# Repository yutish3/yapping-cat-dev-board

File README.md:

this is a custom made esp 32 devboard with extra 128mbit memory so it can do a little more processing then normal
it also has intigrted sensors for temprature and gyromovement sd card slot andd headphone jack
this will fit my custom need of small yet powerful enough custom devboard

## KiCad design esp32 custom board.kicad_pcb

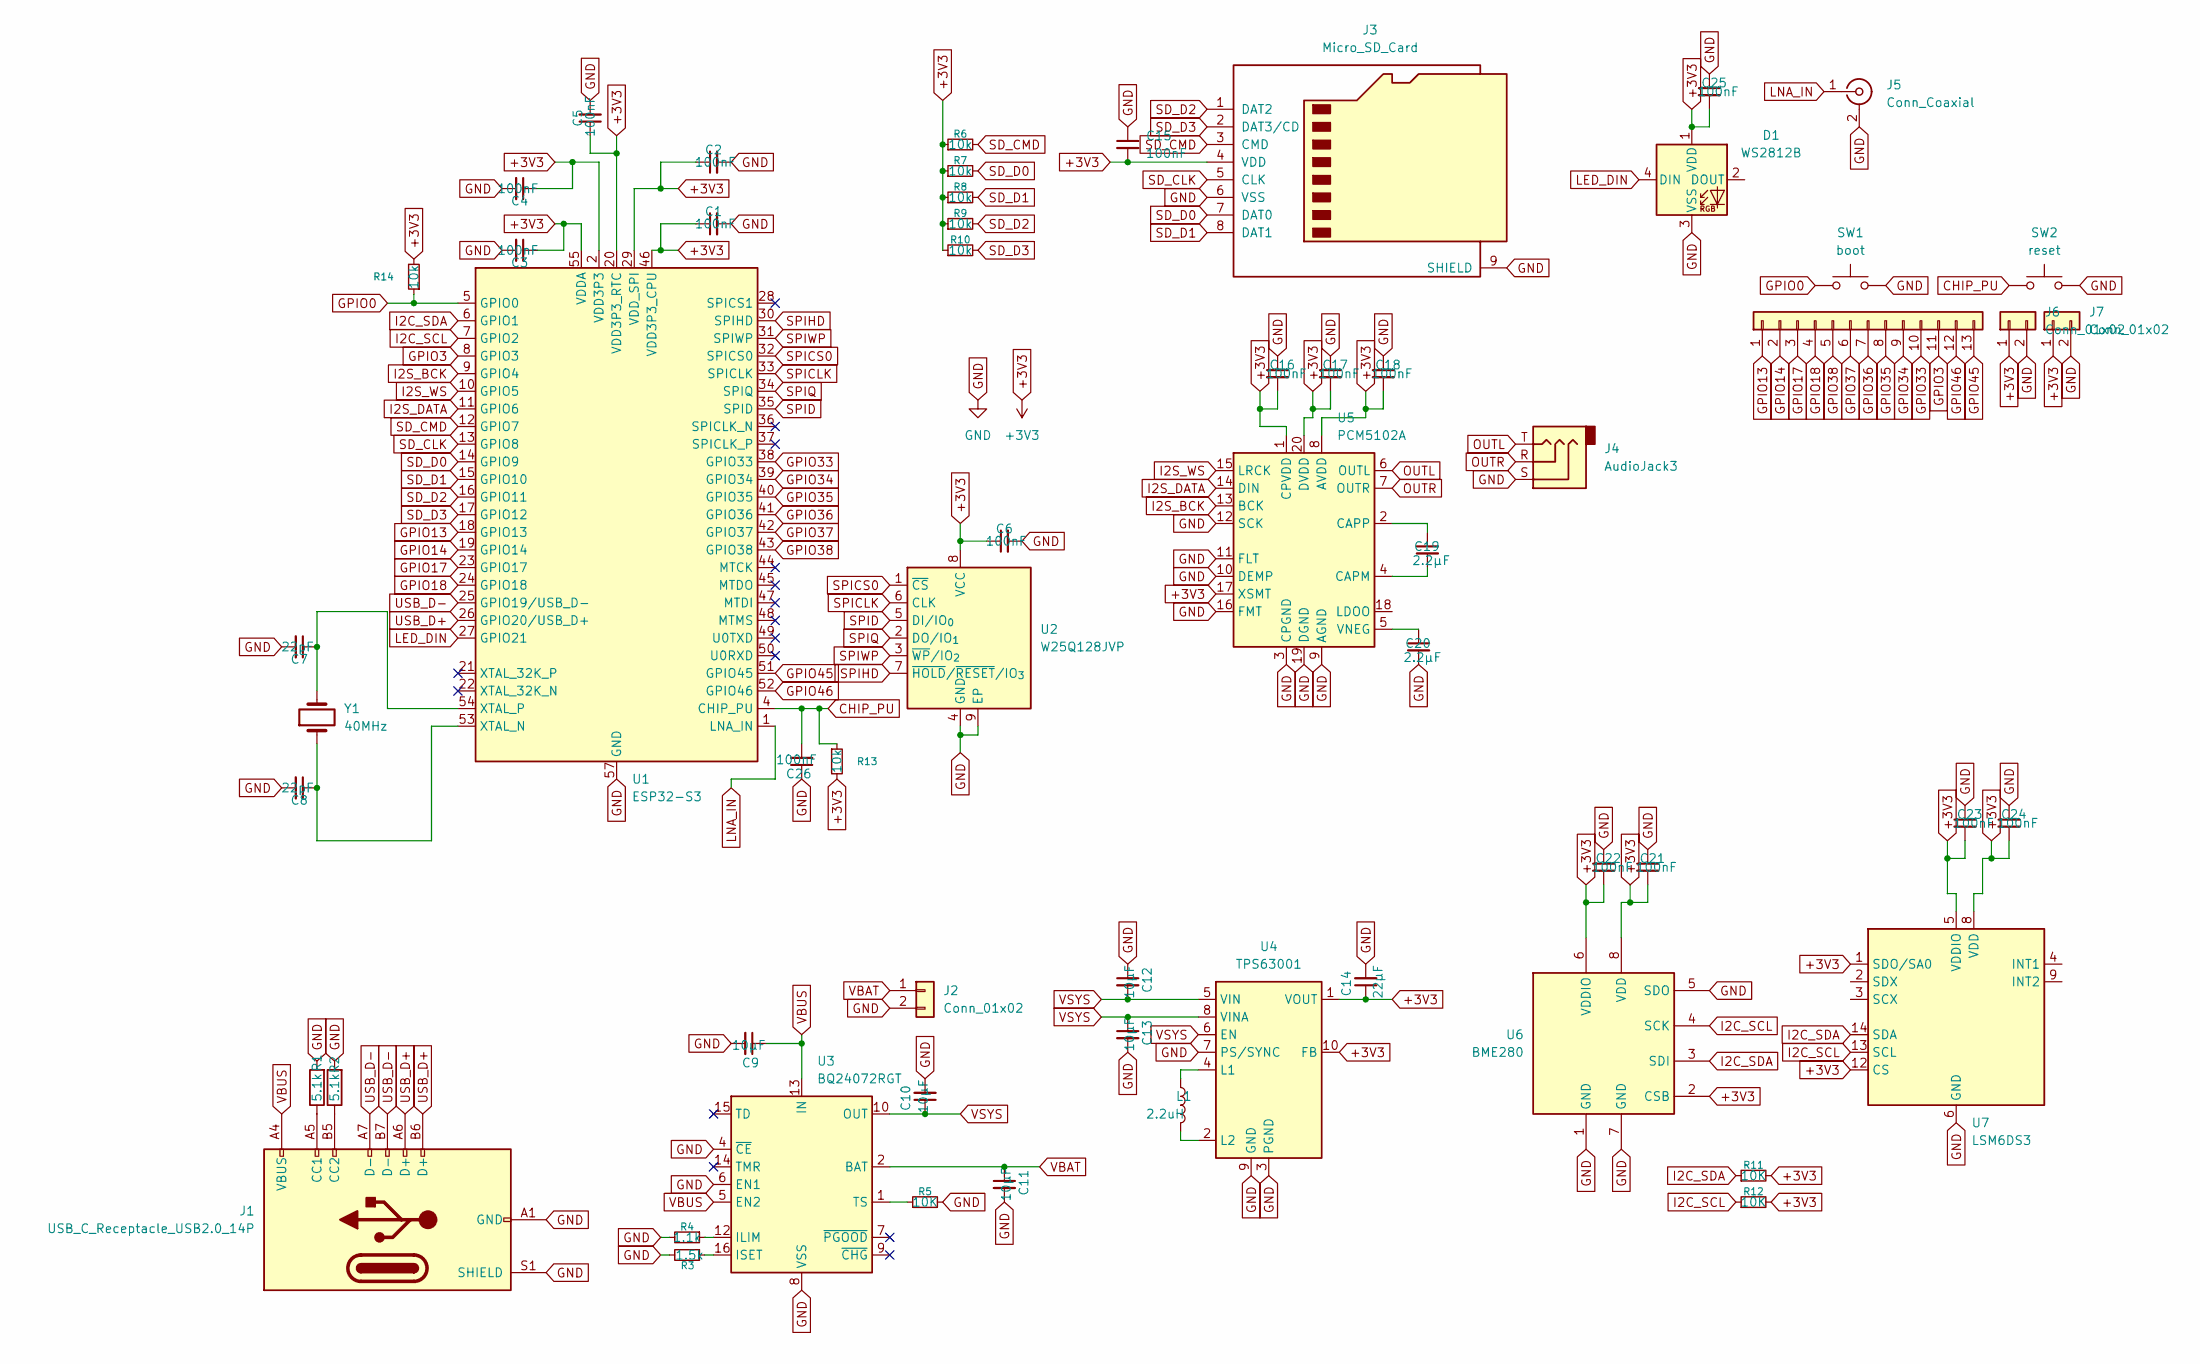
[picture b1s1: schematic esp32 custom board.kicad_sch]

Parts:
C1, C2, C3, C4, C5, C6, C15, C16, C17, C18, C21, C22, C23, C24, C25, C26: 100nF; C_0603_1608Metric
C7, C8: 22pF; C_0603_1608Metric
C9, C10, C11, C12, C13: 10µF; C_0603_1608Metric
C14: 22µF; C_0603_1608Metric
C19, C20: 2.2µF; C_0603_1608Metric
D1: WS2812B; LED_WS2812B_PLCC4_5.0x5.0mm_P3.2mm
J1: USB_C_Receptacle_USB2.0_14P; USB_C_Receptacle_Amphenol_124019772112A
J2: Conn_01x02; JST_PH_S2B-PH-SM4-TB_1x02-1MP_P2.00mm_Horizontal
J3: Micro_SD_Card; microSD_HC_Hirose_DM3AT-SF-PEJM5
J4: AudioJack3; Jack_3.5mm_CUI_SJ-3523-SMT_Horizontal
J5: Conn_Coaxial; U.FL_Hirose_U.FL-R-SMT-1_Vertical
J6, J7: Conn_01x02; PinHeader_1x02_P2.54mm_Vertical
J8: Conn_01x13; PinHeader_1x13_P2.54mm_Vertical
L1: 2.2uH; L_6.3x6.3_H3
R1, R2: 5.1k; R_0603_1608Metric
R3: 1.5k; R_0603_1608Metric
R4: 1.1k; R_0603_1608Metric
R5, R11, R12: 10K; R_0603_1608Metric
R6, R7, R8, R9, R10, R13, R14: 10k; R_0603_1608Metric
SW1: boot; SW_SPST_FSMSM
SW2: reset; SW_SPST_FSMSM
U1: ESP32-S3; QFN-56-1EP_7x7mm_P0.4mm_EP4x4mm
U2: W25Q128JVP; WSON-8-1EP_6x5mm_P1.27mm_EP3.4x4.3mm
U3: BQ24072RGT; VQFN-16-1EP_3x3mm_P0.5mm_EP1.6x1.6mm
U4: TPS63001; Texas_DRC0010J_ThermalVias
U5: PCM5102A; TSSOP-20_4.4x6.5mm_P0.65mm
U6: BME280; Bosch_LGA-8_2.5x2.5mm_P0.65mm_ClockwisePinNumbering
U7: LSM6DS3; LGA-14_3x2.5mm_P0.5mm_LayoutBorder3x4y
Y1: 40MHz; Crystal_SMD_3225-4Pin_3.2x2.5mm

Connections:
+3V3: C1.1, C2.1, C3.1, C4.1, C5.1, C6.1, C14.1, C15.2, C16.2, C17.2, C18.2, C21.2, C22.2, C23.2, C24.2, C25.2, D1.1 (VDD), J3.4 (VDD), J6.1, J7.1, R6.1, R7.1, R8.1, R9.1, R10.1, R11.2, R12.2, R13.2, R14.2, U1.2 (VDD3P3), U1.3 (VDD3P3), U1.20 (VDD3P3_RTC), U1.29 (VDD_SPI), U1.46 (VDD3P3_CPU), U1.55 (VDDA), U1.56 (VDDA), U2.8 (VCC), U4.1 (VOUT), U4.10 (FB), U5.1 (CPVDD), U5.8 (AVDD), U5.17 (XSMT), U5.20 (DVDD), U6.2 (CSB), U6.6 (VDDIO), U6.8 (VDD), U7.1 (SDO/SA0), U7.5 (VDDIO), U7.8 (VDD), U7.12 (CS)
CHIP_PU: C26.2, R13.1, SW2.1, U1.4 (CHIP_PU)
GND: C1.2, C2.2, C3.2, C4.2, C5.2, C6.2, C7.2, C8.2, C9.2, C10.2, C11.2, C12.1, C13.2, C14.2, C15.1, C16.1, C17.1, C18.1, C20.2, C21.1, C22.1, C23.1, C24.1, C25.1, C26.1, D1.3 (VSS), J1.A1 (GND), J1.A12 (GND), J1.B1 (GND), J1.B12 (GND), J1.S1 (SHIELD), J2.2, J3.6 (VSS), J3.9 (SHIELD), J4.S, J5.2 (Ext), J6.2, J7.2, R1.2, R2.2, R3.2, R4.2, R5.2, SW1.2, SW2.2, U1.57 (GND), U2.4 (GND), U2.9 (EP), U3.4 (~CE), U3.6 (EN1), U3.8 (VSS), U3.17 (VSS), U4.3 (PGND), U4.7 (PS/SYNC), U4.9 (GND), U4.11 (PGND), U5.3 (CPGND), U5.9 (AGND), U5.10 (DEMP), U5.11 (FLT), U5.12 (SCK), U5.16 (FMT), U5.19 (DGND), U6.1 (GND), U6.5 (SDO), U6.7 (GND), U7.6 (GND), U7.7 (GND)
GPIO0: R14.1, SW1.1, U1.5 (GPIO0)
GPIO3: J8.11, U1.8 (GPIO3)
GPIO13: J8.1, U1.18 (GPIO13)
GPIO14: J8.2, U1.19 (GPIO14)
GPIO17: J8.3, U1.23 (GPIO17)
GPIO18: J8.4, U1.24 (GPIO18)
GPIO33: J8.10, U1.38 (GPIO33)
GPIO34: J8.9, U1.39 (GPIO34)
GPIO35: J8.8, U1.40 (GPIO35)
GPIO36: J8.7, U1.41 (GPIO36)
GPIO37: J8.6, U1.42 (GPIO37)
GPIO38: J8.5, U1.43 (GPIO38)
GPIO45: J8.13, U1.51 (GPIO45)
GPIO46: J8.12, U1.52 (GPIO46)
I2C_SCL: R12.1, U1.7 (GPIO2), U6.4 (SCK), U7.13 (SCL)
I2C_SDA: R11.1, U1.6 (GPIO1), U6.3 (SDI), U7.14 (SDA)
I2S_BCK: U1.9 (GPIO4), U5.13 (BCK)
I2S_DATA: U1.11 (GPIO6), U5.14 (DIN)
I2S_WS: U1.10 (GPIO5), U5.15 (LRCK)
LED_DIN: D1.4 (DIN), U1.27 (GPIO21)
LNA_IN: J5.1 (In), U1.1 (LNA_IN)
unnamed: J1.A5 (CC1), R1.1
unnamed: J1.B5 (CC2), R2.1
unnamed: C8.1, U1.53 (XTAL_N), Y1.1
unnamed: C7.1, U1.54 (XTAL_P), Y1.2
unnamed: R4.1, U3.12 (ILIM)
unnamed: R3.1, U3.16 (ISET)
unnamed: R5.1, U3.1 (TS)
unnamed: L1.1, U4.4 (L1)
unnamed: L1.2, U4.2 (L2)
unnamed: C19.2, U5.4 (CAPM)
unnamed: C19.1, U5.2 (CAPP)
unnamed: C20.1, U5.5 (VNEG)
OUTL: J4.T, U5.6 (OUTL)
OUTR: J4.R, U5.7 (OUTR)
SD_CLK: J3.5 (CLK), U1.13 (GPIO8)
SD_CMD: J3.3 (CMD), R6.2, U1.12 (GPIO7)
SD_D0: J3.7 (DAT0), R7.2, U1.14 (GPIO9)
SD_D1: J3.8 (DAT1), R8.2, U1.15 (GPIO10)
SD_D2: J3.1 (DAT2), R9.2, U1.16 (GPIO11)
SD_D3: J3.2 (DAT3/CD), R10.2, U1.17 (GPIO12)
SPICLK: U1.33 (SPICLK), U2.6 (CLK)
SPICS0: U1.32 (SPICS0), U2.1 (~CS)
SPID: U1.35 (SPID), U2.5 (DI/IO_{0})
SPIHD: U1.30 (SPIHD), U2.7 (~HOLD/~RESET/IO_{3})
SPIQ: U1.34 (SPIQ), U2.2 (DO/IO_{1})
SPIWP: U1.31 (SPIWP), U2.3 (~WP/IO_{2})
USB_D+: J1.A6 (D+), J1.B6 (D+), U1.26 (GPIO20/USB_D+)
USB_D-: J1.A7 (D-), J1.B7 (D-), U1.25 (GPIO19/USB_D-)
VBAT: C11.1, J2.1, U3.2 (BAT), U3.3 (BAT)
VBUS: C9.1, J1.A4 (VBUS), J1.A9 (VBUS), J1.B4 (VBUS), J1.B9 (VBUS), U3.5 (EN2), U3.13 (IN)
VSYS: C10.1, C12.2, C13.1, U3.10 (OUT), U3.11 (OUT), U4.5 (VIN), U4.6 (EN), U4.8 (VINA)

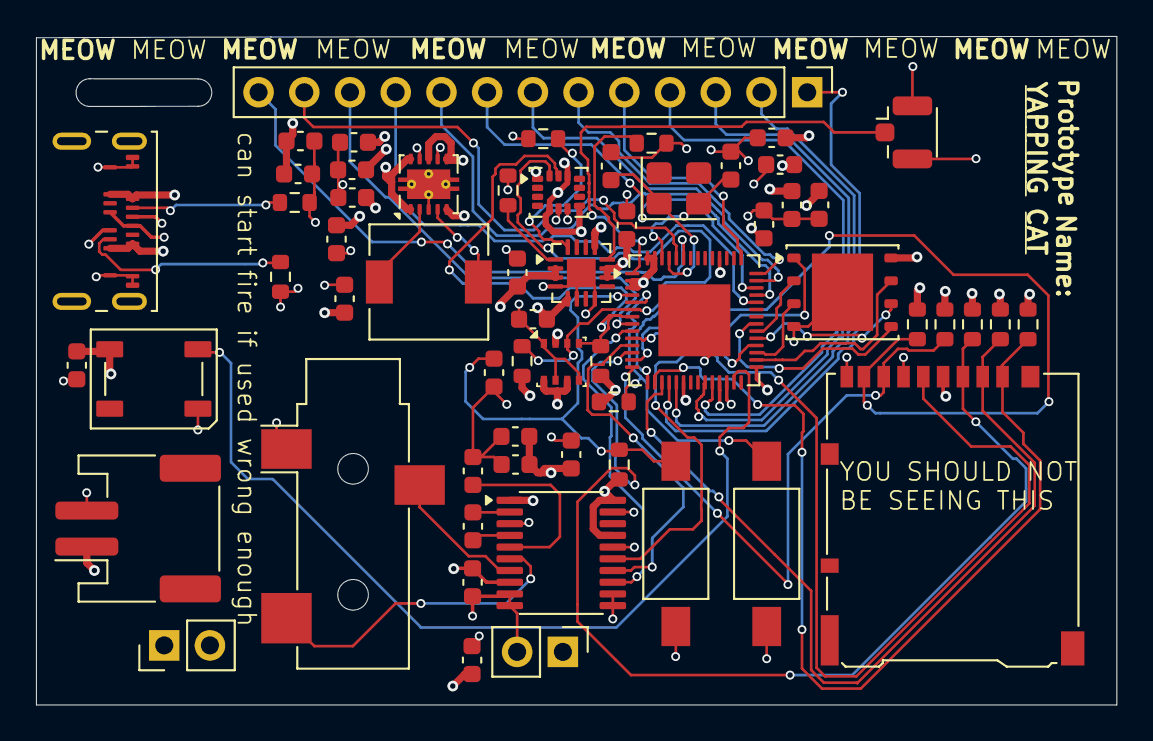
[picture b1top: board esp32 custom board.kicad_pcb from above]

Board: 4 copper layers, 60.0 x 37.1 mm, 60 parts (0 on the bottom side), 55 nets.

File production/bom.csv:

Designator,Footprint,Quantity,Value,LCSC Part #
"C1, C15, C16, C17, C18, C2, C21, C22, C23, C24, C25, C26, C3, C4, C5, C6",0603,16,100nF,
"C10, C11, C12, C13, C9",0603,5,10µF,
C14,0603,1,22µF,
"C19, C20",0603,2,2.2µF,
"C7, C8",0603,2,22pF,
D1,LED_WS2812B_PLCC4_5.0x5.0mm_P3.2mm,1,WS2812B,
J1,USB_C_Receptacle_Amphenol_124019772112A,1,USB_C_Receptacle_USB2.0_14P,
J2,JST_PH_S2B-PH-SM4-TB_1x02-1MP_P2.00mm_Horizontal,1,Conn_01x02,
J3,microSD_HC_Hirose_DM3AT-SF-PEJM5,1,Micro_SD_Card,
J4,Jack_3.5mm_CUI_SJ-3523-SMT_Horizontal,1,AudioJack3,
J5,U.FL_Hirose_U.FL-R-SMT-1_Vertical,1,Conn_Coaxial,
"J6, J7",PinHeader_1x02_P2.54mm_Vertical,2,Conn_01x02,
J8,PinHeader_1x13_P2.54mm_Vertical,1,Conn_01x13,
L1,L_6.3x6.3_H3,1,2.2uH,
"R1, R2",0603,2,5.1k,
"R10, R11, R12, R13, R14, R5, R6, R7, R8, R9",0603,10,10k,
R3,0603,1,1.5k,
R4,0603,1,1.1k,
SW1,SW_SPST_FSMSM,1,boot,
SW2,SW_SPST_FSMSM,1,reset,
U1,QFN-56-1EP_7x7mm_P0.4mm_EP4x4mm,1,ESP32-S3,
U2,WSON-8-1EP_6x5mm_P1.27mm_EP3.4x4.3mm,1,W25Q128JVP,
U3,VQFN-16-1EP_3x3mm_P0.5mm_EP1.6x1.6mm,1,BQ24072RGT,
U4,Texas_DRC0010J_ThermalVias,1,TPS63001,
U5,TSSOP-20_4.4x6.5mm_P0.65mm,1,PCM5102A,
U6,Bosch_LGA-8_2.5x2.5mm_P0.65mm_ClockwisePinNumbering,1,BME280,
U7,LGA-14_3x2.5mm_P0.5mm_LayoutBorder3x4y,1,LSM6DS3,
Y1,Crystal_SMD_3225-4Pin_3.2x2.5mm,1,40MHz,

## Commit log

2026-03-08 Insert images into README.md
    Add images to the README file
2026-03-08 Enhance README with ESP32 devboard details
    Added description of custom ESP32 devboard features and images.
2026-03-08 Update images in README.md
    Removed an old image and added three new images to enhance the README.
